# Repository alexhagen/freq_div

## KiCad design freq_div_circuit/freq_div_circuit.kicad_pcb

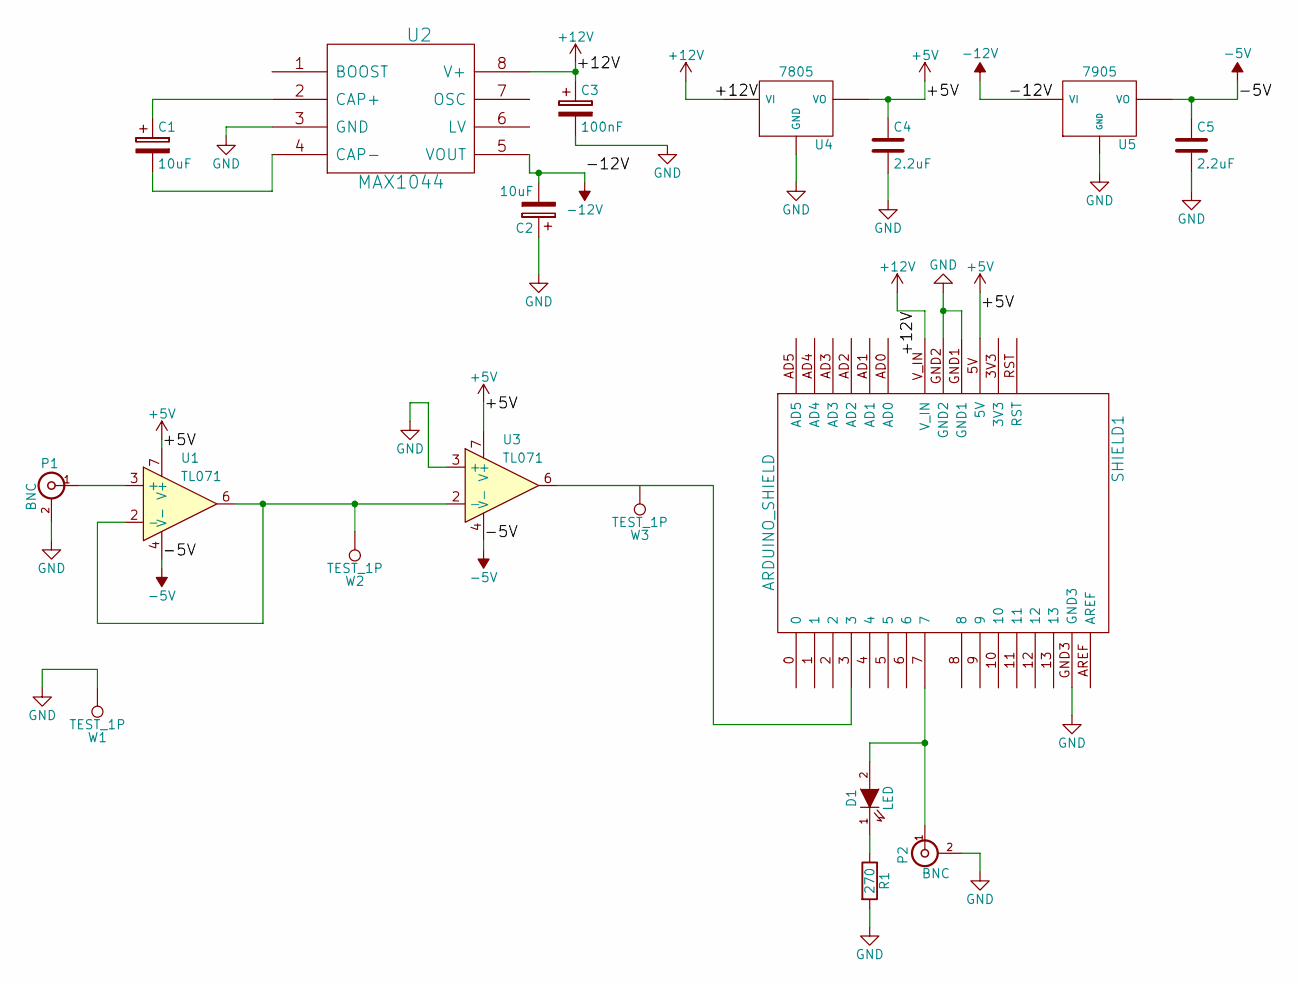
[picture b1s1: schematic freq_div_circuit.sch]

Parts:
C1, C2: 10uF; C_Radial_D5_L11_P2
C3: 100nF; C_Disc_D6_P5
C4, C5: 2.2uF; C_Radial_D5_L11_P2
D1: LED; LED-5MM
P1, P2: BNC; BNC_Socket_TYCO-AMP
R1: 270; Resistor_Horizontal_RM10mm
SHIELD1: ARDUINO_SHIELD; ARDUINO SHIELD
U1: TL071; DIP-8_W7.62mm
U2: MAX1044; DIP-8_W7.62mm
U3: TL071
U4: 7805; TO-220_Neutral123_Vertical
U5: 7905; TO-220_Neutral123_Vertical
W1, W2, W3: TEST_1P; PINTST

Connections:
+5V: C4.1, SHIELD1.5V, U1.7 (V+), U3.7 (V+), U4.VO
+12V: C3.1, SHIELD1.V_IN, U2.8 (V+), U4.VI
-5V: C5.1, U1.4 (V-), U3.4 (V-), U5.VO
-12V: C2.2, U2.5 (VOUT), U5.VI
GND: C2.1, C3.2, C4.2, C5.2, P1.2 (Ext), P2.2 (Ext), R1.2, SHIELD1.GND1, SHIELD1.GND2, SHIELD1.GND3, U2.3 (GND), U3.3 (+), U4.GND, U5.GND, W1.1
unnamed: C1.1, U2.2 (CAP+)
unnamed: C1.2, U2.4 (CAP-)
unnamed: D1.1 (K), R1.1
unnamed: D1.2 (A), P2.1 (In), SHIELD1.7
unnamed: P1.1 (In), U1.3 (+)
unnamed: SHIELD1.3, U3.6
unnamed: U1.2 (-), U1.6, U3.2 (-), W2.1

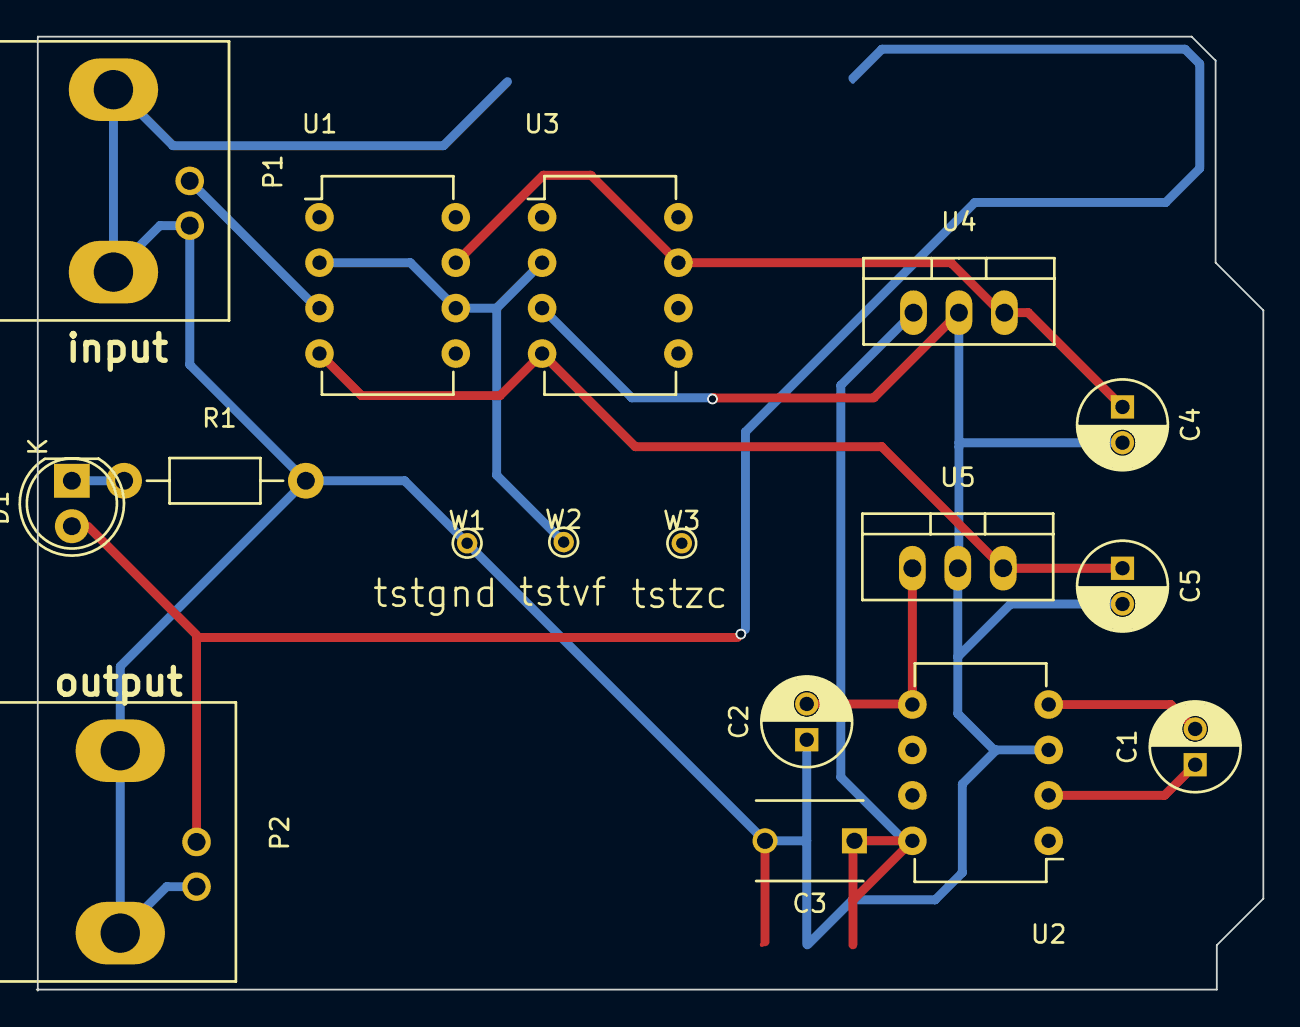
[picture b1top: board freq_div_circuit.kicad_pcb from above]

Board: 2 copper layers, 68.6 x 53.3 mm, 17 parts (0 on the bottom side), 11 nets.

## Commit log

2017-10-30 initial commit with firmware and circuit with bad mcp6001
2017-10-30 updating schematic with tl071cp
2017-11-01 updated by opening
